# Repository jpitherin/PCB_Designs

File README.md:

# PCB_Designs
My designs from PCB design course at Metropolia

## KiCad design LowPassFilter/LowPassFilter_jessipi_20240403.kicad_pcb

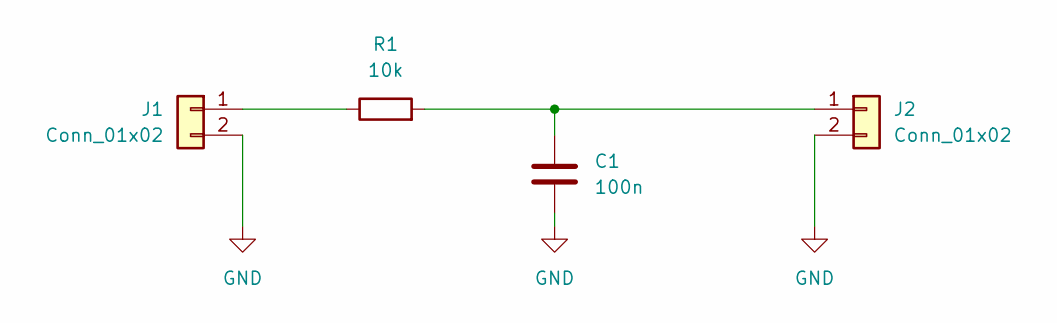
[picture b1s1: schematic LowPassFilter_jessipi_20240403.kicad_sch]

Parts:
C1: 100n; C_Axial_L3.8mm_D2.6mm_P10.00mm_Horizontal
J1, J2: Conn_01x02; PinHeader_1x02_P1.27mm_Vertical
R1: 10k; R_Axial_DIN0204_L3.6mm_D1.6mm_P7.62mm_Horizontal

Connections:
GND: C1.2, J1.2, J2.2
unnamed: J1.1, R1.1
unnamed: C1.1, J2.1, R1.2

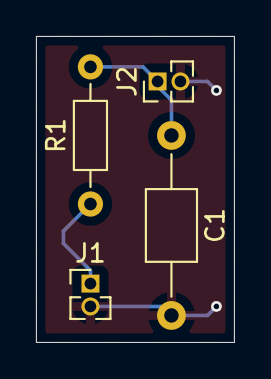
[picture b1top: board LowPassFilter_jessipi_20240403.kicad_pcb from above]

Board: 2 copper layers, 11.0 x 17.0 mm, 4 parts (0 on the bottom side), 3 nets.

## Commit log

2024-04-03 Rename PCB_HW1_jessipi_20240321.kicad_pcb to PCB_HW1/PCB_HW1_jessipi_20240321.kicad_pcb
